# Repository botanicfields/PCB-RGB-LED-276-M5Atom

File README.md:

# PCB-RGB-LED-276-M5Atom
Circle clock using 276pcs of WS2812C-2020 and an M5Atom

## 頒布

[M5Atom 用 RGB LED 276 基板](https://www.switch-science.com/catalog/7039/)

[M5Atom 用 RGB LED 276 基板（丸形）](https://botanicfields.booth.pm/items/2940057)

## 説明書

https://github.com/botanicfields/PCB-RGB-LED-276-M5Atom/blob/main/bf-025_doc.pdf

## RTC 基板の増設

　GROVE コネクタ経由でリアルタイムクロック (RTC) 基板を増設できます。スペーサを用いて 2 階建てにできます。

[M5 用 リアルタイムクロック (RTC) 基板](https://www.switch-science.com/catalog/7170/)

## 置時計のデモ
　置時計のデモを作成しました。RTC に対応しました。RTC がなくても動作します。以下の機能があります。

- 時・分・秒・曜日・年・月・日の表示（スクロール）
- 時・分・秒のアナログ風表示（彗星の尾）
- 文字盤背景色の変化
- デモ: 時刻表示中のデモ (DemoClock)
- デモ: カウントダウンタイマー (DemoTimeShock)
- デモ: ランプテスト表示 (DemoCyron)
- デモ: 色相環表示 (DemoHueRing)
- デモ: パーリンノイズ (DemoNoise)

　時刻表示中のデモには以下があります。

- 文字色の切替（シアン・赤・緑・青）
- フォント表示（記号・数字、英大文字、英小文字）
- テキスト表示（英大文字、英小文字混在）
- エイリアン

　動作中 M5Atom のボタンで以下を操作します。切替の状況はシリアルモニタで確認できます。

|長押し時間|表示|効果|
|:-:|:-:|:-:|
| -  |Pale|カラーパレットを切替|
|>1 秒|Next|デモを切替、【クロックデモ】デモ内容を切替（文字色、フォント）|
|>2 秒|Exit|デモを切替|
|>3 秒|Temp|色温度を切替|
|>4 秒|Corr|色補正を切替|
|>5 秒|Scal|【パーリンノイズデモ】スケール (x, y) を切替|
|>6 秒|Peri|【パーリンノイズデモ】周期 (z) を切替|
|>7 秒|Null|ボタン操作を取消|

　カウントダウンタイマー動作中、M5Atom のボタンで以下を操作します。

|長押し時間|表示|状態|効果|
|:-:|:-:|:-:|:-:|
| - | - |カウントダウン停止中|カウントダウン開始|
| - | - |カウントダウン中|クイズモードに移行、賞金額を表示|
|>1 秒|Stop| - |カウントダウンを中止、初期値に戻す|
|>2 秒|Time| - |カウントダウンを中止、初期値を変更|
|>3 秒|Pale| - |カラーパレットを変更|
|>4 秒|Exit| - |終了、デモを切替|
|>5 秒|Null| - |ボタン操作を取消|

## 解説 Explanation
"Circle LED Clock by M5Atom and FastLED" in Japanese

[M5Atom と FastLED で 円形 LED 時計を作る](https://qiita.com/BotanicFields/items/a1e182f418d5a07120ac)

## YouTube: Clock Demonstration 

[Clock Demo on BF-025: RGB-LED 276 for M5Atom](https://youtu.be/55dffut1Fk0)

## 3D images by KiCad:

## YouTube: Examples

[ColorPalette an example from FastLED on BF-025: RGB-LED 276 for M5Atom](https://youtu.be/OUliTGfqcDM)

[DemoReel100 an example from FastLED on BF-025 RGB-LED 276 for M5Atom](https://youtu.be/VHuoHDQSU5E)

[Pacifica an example from FastLED on BF-025 RGB-LED 276 for M5Atom](https://youtu.be/MY5FGuDM8ZY)

[Pride2015 an example from FastLED on BF-025: RGB-LED 276 for M5Atom](https://youtu.be/uj7ePEQMkhk)

[TwinkleFox an exmaple from FastLED on BF025: RGB-LED 276 for M5Atom](https://youtu.be/3NwbCFiiEbc)

## Discussions

[JLCPCB official user group facebook](https://www.facebook.com/groups/JLCPCB/permalink/837468943770299/)

## Practical status of gerber, BOM, pick & place

### V02L01

- JLCPCB: OK

### V03L01

- ALLPCB: OK
- Seeed FusionPCB: OK

### V03L02

- ALLPCB: OK
- JLCPCB: OK

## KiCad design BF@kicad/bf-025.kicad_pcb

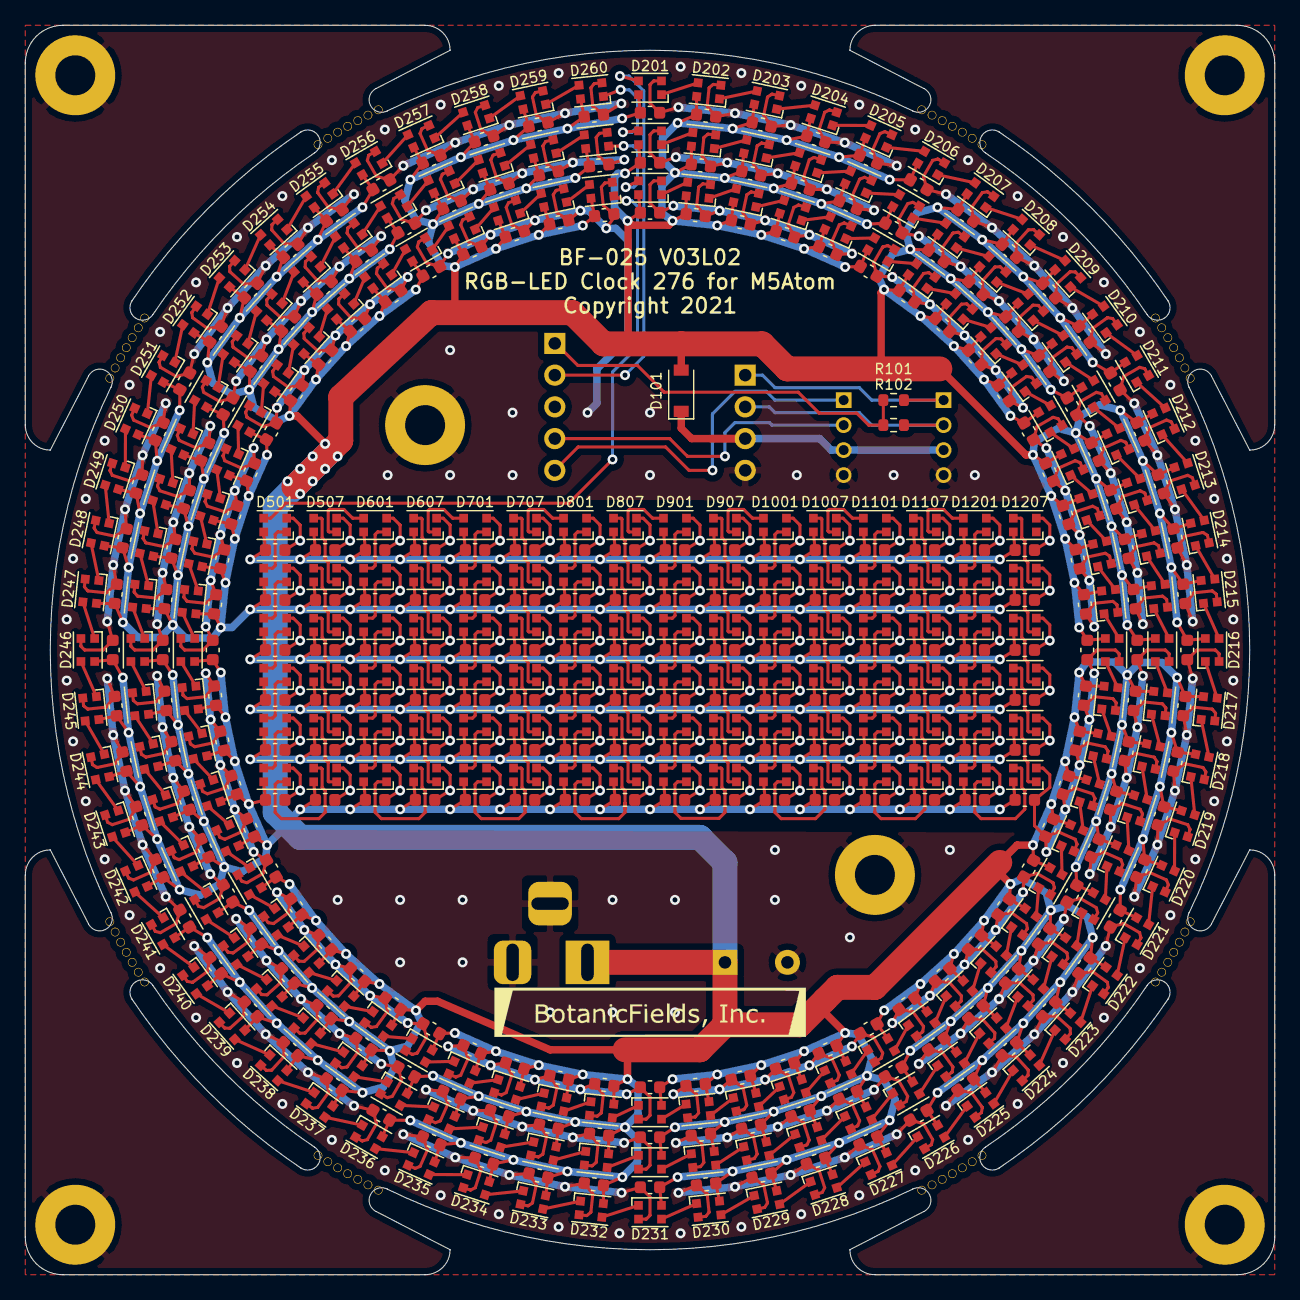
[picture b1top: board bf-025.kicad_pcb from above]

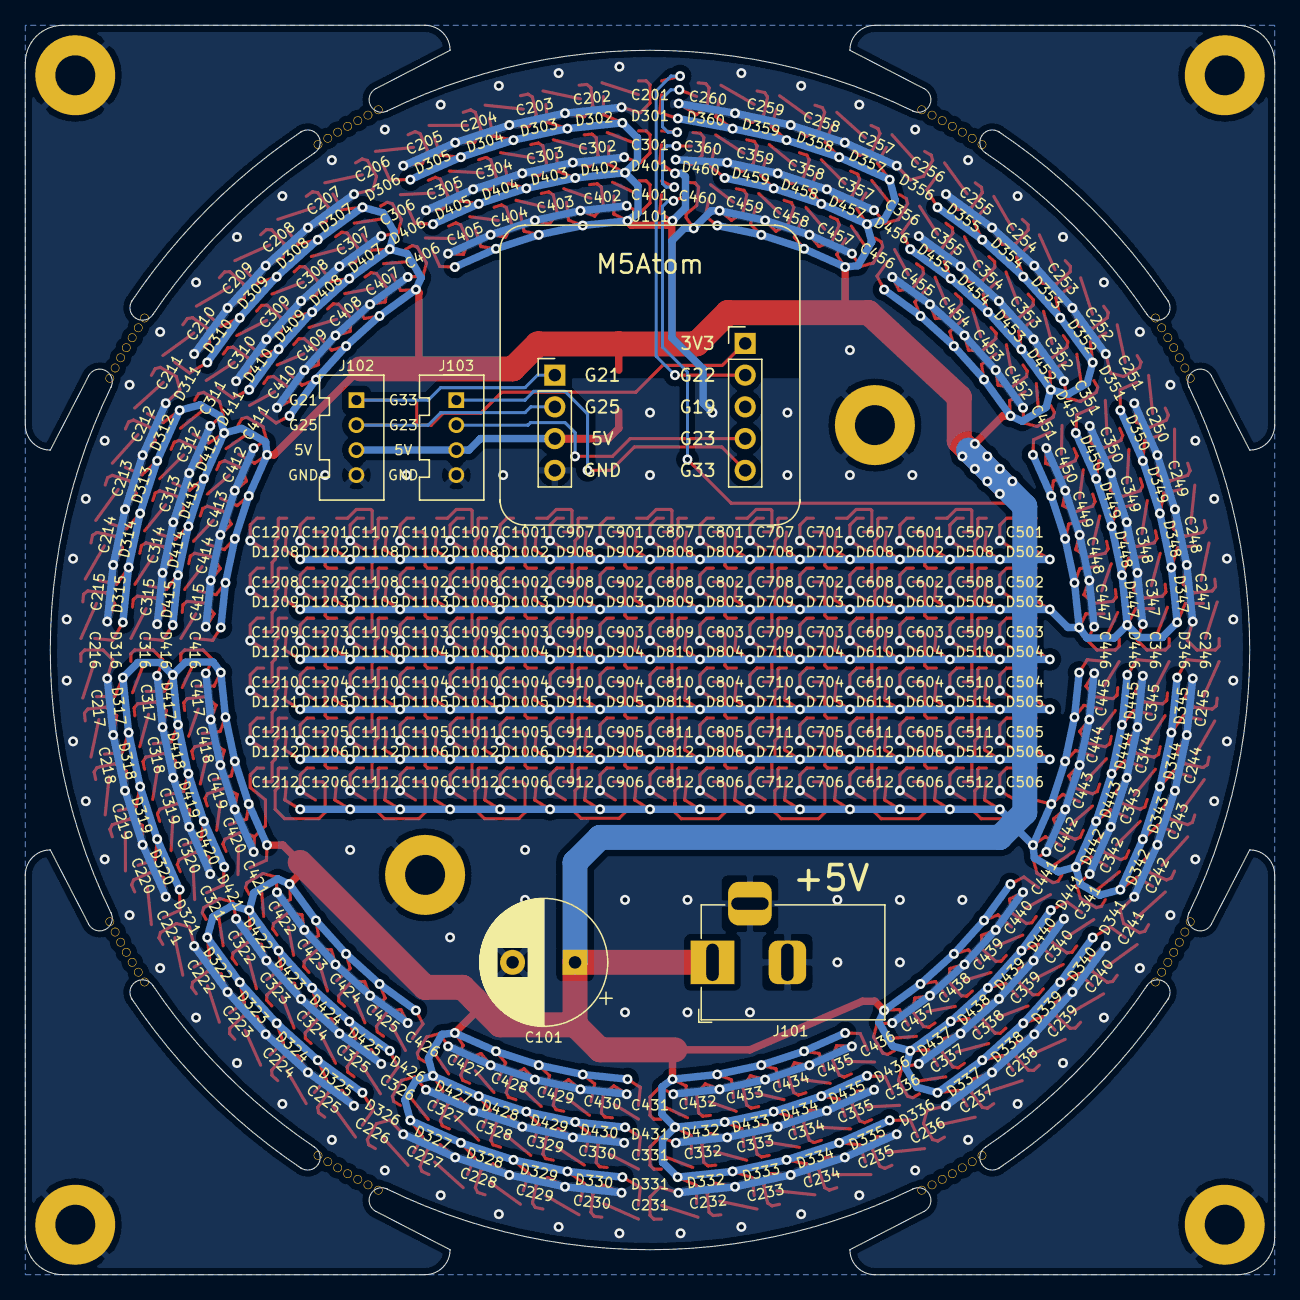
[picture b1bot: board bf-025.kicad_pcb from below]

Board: 2 copper layers, 100.0 x 100.0 mm, 560 parts (5 on the bottom side), 284 nets.

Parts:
C101: 1000u; CP_Radial_D10.0mm_P5.00mm
C201, C202, C203, C204, C205, C206, C207, C208, C209, C210, C211, C212, C213, C214, C215, C216, C217, C218, C219, C220, C221, C222, C223, C224, C225, C226, C227, C228, C229, C230, C231, C232, C233, C234, C235, C236, C237, C238, C239, C240, C241, C242, C243, C244, C245, C246, C247, C248, C249, C250, C251, C252, C253, C254, C255, C256, C257, C258, C259, C260, C301, C302, C303, C304, C305, C306, C307, C308, C309, C310, C311, C312, C313, C314, C315, C316, C317, C318, C319, C320, C321, C322, C323, C324, C325, C326, C327, C328, C329, C330, C331, C332, C333, C334, C335, C336, C337, C338, C339, C340, C341, C342, C343, C344, C345, C346, C347, C348, C349, C350, C351, C352, C353, C354, C355, C356, C357, C358, C359, C360, C401, C402, C403, C404, C405, C406, C407, C408, C409, C410, C411, C412, C413, C414, C415, C416, C417, C418, C419, C420, C421, C422, C423, C424, C425, C426, C427, C428, C429, C430, C431, C432, C433, C434, C435, C436, C437, C438, C439, C440, C441, C442, C443, C444, C445, C446, C447, C448, C449, C450, C451, C452, C453, C454, C455, C456, C457, C458, C459, C460, C501, C502, C503, C504, C505, C506, C507, C508, C509, C510, C511, C512, C601, C602, C603, C604, C605, C606, C607, C608, C609, C610, C611, C612, C701, C702, C703, C704, C705, C706, C707, C708, C709, C710, C711, C712, C801, C802, C803, C804, C805, C806, C807, C808, C809, C810, C811, C812, C901, C902, C903, C904, C905, C906, C907, C908, C909, C910, C911, C912, C1001, C1002, C1003, C1004, C1005, C1006, C1007, C1008, C1009, C1010, C1011, C1012, C1101, C1102, C1103, C1104, C1105, C1106, C1107, C1108, C1109, C1110, C1111, C1112, C1201, C1202, C1203, C1204, C1205, C1206, C1207, C1208, C1209, C1210, C1211, C1212: 100n; C_0603_1608Metric
D101: B5819W; D_SOD-123
D201, D202, D203, D204, D205, D206, D207, D208, D209, D210, D211, D212, D213, D214, D215, D216, D217, D218, D219, D220, D221, D222, D223, D224, D225, D226, D227, D228, D229, D230, D231, D232, D233, D234, D235, D236, D237, D238, D239, D240, D241, D242, D243, D244, D245, D246, D247, D248, D249, D250, D251, D252, D253, D254, D255, D256, D257, D258, D259, D260, D301, D302, D303, D304, D305, D306, D307, D308, D309, D310, D311, D312, D313, D314, D315, D316, D317, D318, D319, D320, D321, D322, D323, D324, D325, D326, D327, D328, D329, D330, D331, D332, D333, D334, D335, D336, D337, D338, D339, D340, D341, D342, D343, D344, D345, D346, D347, D348, D349, D350, D351, D352, D353, D354, D355, D356, D357, D358, D359, D360, D401, D402, D403, D404, D405, D406, D407, D408, D409, D410, D411, D412, D413, D414, D415, D416, D417, D418, D419, D420, D421, D422, D423, D424, D425, D426, D427, D428, D429, D430, D431, D432, D433, D434, D435, D436, D437, D438, D439, D440, D441, D442, D443, D444, D445, D446, D447, D448, D449, D450, D451, D452, D453, D454, D455, D456, D457, D458, D459, D460, D501, D502, D503, D504, D505, D506, D507, D508, D509, D510, D511, D512, D601, D602, D603, D604, D605, D606, D607, D608, D609, D610, D611, D612, D701, D702, D703, D704, D705, D706, D707, D708, D709, D710, D711, D712, D801, D802, D803, D804, D805, D806, D807, D808, D809, D810, D811, D812, D901, D902, D903, D904, D905, D906, D907, D908, D909, D910, D911, D912, D1001, D1002, D1003, D1004, D1005, D1006, D1007, D1008, D1009, D1010, D1011, D1012, D1101, D1102, D1103, D1104, D1105, D1106, D1107, D1108, D1109, D1110, D1111, D1112, D1201, D1202, D1203, D1204, D1205, D1206, D1207, D1208, D1209, D1210, D1211, D1212: WS2812C-2020; BF@WS2812C-2020
J101: Barrel_Jack_Switch; BF@BarrelJack_Horizontal
J102: I2C; HW4-2.0
J103: UART; HW4-2.0
R101, R102: 10k; R_0603_1608Metric
U101: M5Atom; BF@M5Atom

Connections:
+5V: C101.1, C201.1, C202.1, C203.1, C204.1, C205.1, C206.1, C207.1, C208.1, C209.1, C210.1, C211.1, C212.1, C213.1, C214.1, C215.1, C216.1, C217.1, C218.1, C219.1, C220.1, C221.1, C222.1, C223.1, C224.1, C225.1, C226.1, C227.1, C228.1, C229.1, C230.1, C231.1, C232.1, C233.1, C234.1, C235.1, C236.1, C237.1, C238.1, C239.1, C240.1, C241.1, C242.1, C243.1, C244.1, C245.1, C246.1, C247.1, C248.1, C249.1, C250.1, C251.1, C252.1, C253.1, C254.1, C255.1, C256.1, C257.1, C258.1, C259.1, C260.1, C301.1, C302.1, C303.1, C304.1, C305.1, C306.1, C307.1, C308.1, C309.1, C310.1, C311.1, C312.1, C313.1, C314.1, C315.1, C316.1, C317.1, C318.1, C319.1, C320.1, C321.1, C322.1, C323.1, C324.1, C325.1, C326.1, C327.1, C328.1, C329.1, C330.1, C331.1, C332.1, C333.1, C334.1, C335.1, C336.1, C337.1, C338.1, C339.1, C340.1, C341.1, C342.1, C343.1, C344.1, C345.1, C346.1, C347.1, C348.1, C349.1, C350.1, C351.1, C352.1, C353.1, C354.1, C355.1, C356.1, C357.1, C358.1, C359.1, C360.1, C401.1, C402.1, C403.1, C404.1, C405.1, C406.1, C407.1, C408.1, C409.1, C410.1, C411.1, C412.1, C413.1, C414.1, C415.1, C416.1, C417.1, C418.1, C419.1, C420.1, C421.1, C422.1, C423.1, C424.1, C425.1, C426.1, C427.1, C428.1, C429.1, C430.1, C431.1, C432.1, C433.1, C434.1, C435.1, C436.1, C437.1, C438.1, C439.1, C440.1, C441.1, C442.1, C443.1, C444.1, C445.1, C446.1, C447.1, C448.1, C449.1, C450.1, C451.1, C452.1, C453.1, C454.1, C455.1, C456.1, C457.1, C458.1, C459.1, C460.1, C501.1, C502.1, C503.1, C504.1, C505.1, C506.1, C507.1, C508.1, C509.1, C510.1, C511.1, C512.1, C601.1, C602.1, C603.1, C604.1, C605.1, C606.1, C607.1, C608.1, C609.1, C610.1, C611.1, C612.1, C701.1, C702.1, C703.1, C704.1, C705.1, C706.1, C707.1, C708.1, C709.1, C710.1, C711.1, C712.1, C801.1, C802.1, C803.1, C804.1, C805.1, C806.1, C807.1, C808.1, C809.1, C810.1, C811.1, C812.1, C901.1, C902.1, C903.1, C904.1, C905.1, C906.1, C907.1, C908.1, C909.1, C910.1, C911.1, C912.1, C1001.1, C1002.1, C1003.1, C1004.1, C1005.1, C1006.1, C1007.1, C1008.1, C1009.1, C1010.1, C1011.1, C1012.1, C1101.1, C1102.1, C1103.1, C1104.1, C1105.1, C1106.1, C1107.1, C1108.1, C1109.1, C1110.1, C1111.1, C1112.1, C1201.1, C1202.1, C1203.1, C1204.1, C1205.1, C1206.1, C1207.1, C1208.1, C1209.1, C1210.1, C1211.1, C1212.1, D101.2, D201.4, D202.4, D203.4, D204.4, D205.4, D206.4, D207.4, D208.4, D209.4, D210.4, D211.4, D212.4, D213.4, D214.4, D215.4, D216.4, D217.4, D218.4, D219.4, D220.4, D221.4, D222.4, D223.4, D224.4, D225.4, D226.4, D227.4, D228.4, D229.4, D230.4, D231.4, D232.4, D233.4, D234.4, D235.4, D236.4, D237.4, D238.4, D239.4, D240.4, D241.4, D242.4, D243.4, D244.4, D245.4, D246.4, D247.4, D248.4, D249.4, D250.4, D251.4, D252.4, D253.4, D254.4, D255.4, D256.4, D257.4, D258.4, D259.4, D260.4, D301.4, D302.4, D303.4, D304.4, D305.4, D306.4, D307.4, D308.4, D309.4, D310.4, D311.4, D312.4, D313.4, D314.4, D315.4, D316.4, D317.4, D318.4, D319.4, D320.4, D321.4, D322.4, D323.4, D324.4, D325.4, D326.4, D327.4, D328.4, D329.4, D330.4, D331.4, D332.4, D333.4, D334.4, D335.4, D336.4, D337.4, D338.4, D339.4, D340.4, D341.4, D342.4, D343.4, D344.4, D345.4, D346.4, D347.4, D348.4, D349.4, D350.4, D351.4, D352.4, D353.4, D354.4, D355.4, D356.4, D357.4, D358.4, D359.4, D360.4, D401.4, D402.4, D403.4, D404.4, D405.4, D406.4, D407.4, D408.4, D409.4, D410.4, D411.4, D412.4, D413.4, D414.4, D415.4, D416.4, D417.4, D418.4, D419.4, D420.4, D421.4, D422.4, D423.4, D424.4, D425.4, D426.4, D427.4, D428.4, D429.4, D430.4, D431.4, D432.4, D433.4, D434.4, D435.4, D436.4, D437.4, D438.4, D439.4, D440.4, D441.4, D442.4, D443.4, D444.4, D445.4, D446.4, D447.4, D448.4, D449.4, D450.4, D451.4, D452.4, D453.4, D454.4, D455.4, D456.4, D457.4, D458.4, D459.4, D460.4, D501.4, D502.4, D503.4, D504.4, D505.4, D506.4, D507.4, D508.4, D509.4, D510.4, D511.4, D512.4, D601.4, D602.4, D603.4, D604.4, D605.4, D606.4, D607.4, D608.4, D609.4, D610.4, D611.4, D612.4, D701.4, D702.4, D703.4, D704.4, D705.4, D706.4, D707.4, D708.4, D709.4, D710.4, D711.4, D712.4, D801.4, D802.4, D803.4, D804.4, D805.4, D806.4, D807.4, D808.4, D809.4, D810.4, D811.4, D812.4, D901.4, D902.4, D903.4, D904.4, D905.4, D906.4, D907.4, D908.4, D909.4, D910.4, D911.4, D912.4, D1001.4, D1002.4, D1003.4, D1004.4, D1005.4, D1006.4, D1007.4, D1008.4, D1009.4, D1010.4, D1011.4, D1012.4, D1101.4, D1102.4, D1103.4, D1104.4, D1105.4, D1106.4, D1107.4, D1108.4, D1109.4, D1110.4, D1111.4, D1112.4, D1201.4, D1202.4, D1203.4, D1204.4, D1205.4, D1206.4, D1207.4, D1208.4, D1209.4, D1210.4, D1211.4, D1212.4, J101.1
/G21: J102.1, R101.2, U101.1
/G23_G34: J103.2, U101.6
/G25: J102.2, R102.2, U101.2
/G33: J103.1, U101.5
/M5_3V3: R101.1, R102.1, U101.9
/M5_5V: D101.1, J102.3, J103.3, U101.3
/WS2812C_12_1/DI: D460.1, D501.3
/WS2812C_12_2/DI: D507.1, D601.3
/WS2812C_12_3/DI: D607.1, D701.3
/WS2812C_12_4/DI: D707.1, D801.3
/WS2812C_12_5/DI: D807.1, D901.3
/WS2812C_12_6/DI: D907.1, D1001.3
/WS2812C_12_7/DI: D1007.1, D1101.3
/WS2812C_12_8/DI: D1107.1, D1201.3
/WS2812C_60_1/DIN: D201.3, U101.8
/WS2812C_60_2/DIN: D260.1, D301.3
/WS2812C_60_3/DIN: D360.1, D401.3
GND: C101.2, C201.2, C202.2, C203.2, C204.2, C205.2, C206.2, C207.2, C208.2, C209.2, C210.2, C211.2, C212.2, C213.2, C214.2, C215.2, C216.2, C217.2, C218.2, C219.2, C220.2, C221.2, C222.2, C223.2, C224.2, C225.2, C226.2, C227.2, C228.2, C229.2, C230.2, C231.2, C232.2, C233.2, C234.2, C235.2, C236.2, C237.2, C238.2, C239.2, C240.2, C241.2, C242.2, C243.2, C244.2, C245.2, C246.2, C247.2, C248.2, C249.2, C250.2, C251.2, C252.2, C253.2, C254.2, C255.2, C256.2, C257.2, C258.2, C259.2, C260.2, C301.2, C302.2, C303.2, C304.2, C305.2, C306.2, C307.2, C308.2, C309.2, C310.2, C311.2, C312.2, C313.2, C314.2, C315.2, C316.2, C317.2, C318.2, C319.2, C320.2, C321.2, C322.2, C323.2, C324.2, C325.2, C326.2, C327.2, C328.2, C329.2, C330.2, C331.2, C332.2, C333.2, C334.2, C335.2, C336.2, C337.2, C338.2, C339.2, C340.2, C341.2, C342.2, C343.2, C344.2, C345.2, C346.2, C347.2, C348.2, C349.2, C350.2, C351.2, C352.2, C353.2, C354.2, C355.2, C356.2, C357.2, C358.2, C359.2, C360.2, C401.2, C402.2, C403.2, C404.2, C405.2, C406.2, C407.2, C408.2, C409.2, C410.2, C411.2, C412.2, C413.2, C414.2, C415.2, C416.2, C417.2, C418.2, C419.2, C420.2, C421.2, C422.2, C423.2, C424.2, C425.2, C426.2, C427.2, C428.2, C429.2, C430.2, C431.2, C432.2, C433.2, C434.2, C435.2, C436.2, C437.2, C438.2, C439.2, C440.2, C441.2, C442.2, C443.2, C444.2, C445.2, C446.2, C447.2, C448.2, C449.2, C450.2, C451.2, C452.2, C453.2, C454.2, C455.2, C456.2, C457.2, C458.2, C459.2, C460.2, C501.2, C502.2, C503.2, C504.2, C505.2, C506.2, C507.2, C508.2, C509.2, C510.2, C511.2, C512.2, C601.2, C602.2, C603.2, C604.2, C605.2, C606.2, C607.2, C608.2, C609.2, C610.2, C611.2, C612.2, C701.2, C702.2, C703.2, C704.2, C705.2, C706.2, C707.2, C708.2, C709.2, C710.2, C711.2, C712.2, C801.2, C802.2, C803.2, C804.2, C805.2, C806.2, C807.2, C808.2, C809.2, C810.2, C811.2, C812.2, C901.2, C902.2, C903.2, C904.2, C905.2, C906.2, C907.2, C908.2, C909.2, C910.2, C911.2, C912.2, C1001.2, C1002.2, C1003.2, C1004.2, C1005.2, C1006.2, C1007.2, C1008.2, C1009.2, C1010.2, C1011.2, C1012.2, C1101.2, C1102.2, C1103.2, C1104.2, C1105.2, C1106.2, C1107.2, C1108.2, C1109.2, C1110.2, C1111.2, C1112.2, C1201.2, C1202.2, C1203.2, C1204.2, C1205.2, C1206.2, C1207.2, C1208.2, C1209.2, C1210.2, C1211.2, C1212.2, D201.2, D202.2, D203.2, D204.2, D205.2, D206.2, D207.2, D208.2, D209.2, D210.2, D211.2, D212.2, D213.2, D214.2, D215.2, D216.2, D217.2, D218.2, D219.2, D220.2, D221.2, D222.2, D223.2, D224.2, D225.2, D226.2, D227.2, D228.2, D229.2, D230.2, D231.2, D232.2, D233.2, D234.2, D235.2, D236.2, D237.2, D238.2, D239.2, D240.2, D241.2, D242.2, D243.2, D244.2, D245.2, D246.2, D247.2, D248.2, D249.2, D250.2, D251.2, D252.2, D253.2, D254.2, D255.2, D256.2, D257.2, D258.2, D259.2, D260.2, D301.2, D302.2, D303.2, D304.2, D305.2, D306.2, D307.2, D308.2, D309.2, D310.2, D311.2, D312.2, D313.2, D314.2, D315.2, D316.2, D317.2, D318.2, D319.2, D320.2, D321.2, D322.2, D323.2, D324.2, D325.2, D326.2, D327.2, D328.2, D329.2, D330.2, D331.2, D332.2, D333.2, D334.2, D335.2, D336.2, D337.2, D338.2, D339.2, D340.2, D341.2, D342.2, D343.2, D344.2, D345.2, D346.2, D347.2, D348.2, D349.2, D350.2, D351.2, D352.2, D353.2, D354.2, D355.2, D356.2, D357.2, D358.2, D359.2, D360.2, D401.2, D402.2, D403.2, D404.2, D405.2, D406.2, D407.2, D408.2, D409.2, D410.2, D411.2, D412.2, D413.2, D414.2, D415.2, D416.2, D417.2, D418.2, D419.2, D420.2, D421.2, D422.2, D423.2, D424.2, D425.2, D426.2, D427.2, D428.2, D429.2, D430.2, D431.2, D432.2, D433.2, D434.2, D435.2, D436.2, D437.2, D438.2, D439.2, D440.2, D441.2, D442.2, D443.2, D444.2, D445.2, D446.2, D447.2, D448.2, D449.2, D450.2, D451.2, D452.2, D453.2, D454.2, D455.2, D456.2, D457.2, D458.2, D459.2, D460.2, D501.2, D502.2, D503.2, D504.2, D505.2, D506.2, D507.2, D508.2, D509.2, D510.2, D511.2, D512.2, D601.2, D602.2, D603.2, D604.2, D605.2, D606.2, D607.2, D608.2, D609.2, D610.2, D611.2, D612.2, D701.2, D702.2, D703.2, D704.2, D705.2, D706.2, D707.2, D708.2, D709.2, D710.2, D711.2, D712.2, D801.2, D802.2, D803.2, D804.2, D805.2, D806.2, D807.2, D808.2, D809.2, D810.2, D811.2, D812.2, D901.2, D902.2, D903.2, D904.2, D905.2, D906.2, D907.2, D908.2, D909.2, D910.2, D911.2, D912.2, D1001.2, D1002.2, D1003.2, D1004.2, D1005.2, D1006.2, D1007.2, D1008.2, D1009.2, D1010.2, D1011.2, D1012.2, D1101.2, D1102.2, D1103.2, D1104.2, D1105.2, D1106.2, D1107.2, D1108.2, D1109.2, D1110.2, D1111.2, D1112.2, D1201.2, D1202.2, D1203.2, D1204.2, D1205.2, D1206.2, D1207.2, D1208.2, D1209.2, D1210.2, D1211.2, D1212.2, J101.2, J101.3, J102.4, J103.4, U101.4
unnamed: D201.1, D202.3
unnamed: D202.1, D203.3
unnamed: D203.1, D204.3
unnamed: D204.1, D205.3
unnamed: D205.1, D206.3
unnamed: D206.1, D207.3
unnamed: D207.1, D208.3
unnamed: D208.1, D209.3
unnamed: D209.1, D210.3
unnamed: D210.1, D211.3
unnamed: D211.1, D212.3
unnamed: D212.1, D213.3
unnamed: D213.1, D214.3
unnamed: D214.1, D215.3
unnamed: D215.1, D216.3
unnamed: D216.1, D217.3
unnamed: D217.1, D218.3
unnamed: D218.1, D219.3
unnamed: D219.1, D220.3
unnamed: D220.1, D221.3
unnamed: D221.1, D222.3
unnamed: D222.1, D223.3
unnamed: D223.1, D224.3
unnamed: D224.1, D225.3
unnamed: D225.1, D226.3
unnamed: D226.1, D227.3
unnamed: D227.1, D228.3
unnamed: D228.1, D229.3
unnamed: D229.1, D230.3
unnamed: D230.1, D231.3
unnamed: D231.1, D232.3
unnamed: D232.1, D233.3
unnamed: D233.1, D234.3
unnamed: D234.1, D235.3
unnamed: D235.1, D236.3
unnamed: D236.1, D237.3
unnamed: D237.1, D238.3
unnamed: D238.1, D239.3
unnamed: D239.1, D240.3
unnamed: D240.1, D241.3
unnamed: D241.1, D242.3
unnamed: D242.1, D243.3
unnamed: D243.1, D244.3
unnamed: D244.1, D245.3
unnamed: D245.1, D246.3
unnamed: D246.1, D247.3
unnamed: D247.1, D248.3
unnamed: D248.1, D249.3
unnamed: D249.1, D250.3
unnamed: D250.1, D251.3
unnamed: D251.1, D252.3
unnamed: D252.1, D253.3
unnamed: D253.1, D254.3
unnamed: D254.1, D255.3
unnamed: D255.1, D256.3
unnamed: D256.1, D257.3
unnamed: D257.1, D258.3
unnamed: D258.1, D259.3
unnamed: D259.1, D260.3
unnamed: D301.1, D302.3
unnamed: D302.1, D303.3
unnamed: D303.1, D304.3
unnamed: D304.1, D305.3
unnamed: D305.1, D306.3
unnamed: D306.1, D307.3
unnamed: D307.1, D308.3
unnamed: D308.1, D309.3
unnamed: D309.1, D310.3
unnamed: D310.1, D311.3
unnamed: D311.1, D312.3
unnamed: D312.1, D313.3
unnamed: D313.1, D314.3
unnamed: D314.1, D315.3
unnamed: D315.1, D316.3
unnamed: D316.1, D317.3
unnamed: D317.1, D318.3
unnamed: D318.1, D319.3
unnamed: D319.1, D320.3
unnamed: D320.1, D321.3
unnamed: D321.1, D322.3
unnamed: D322.1, D323.3
unnamed: D323.1, D324.3
unnamed: D324.1, D325.3
unnamed: D325.1, D326.3
unnamed: D326.1, D327.3
unnamed: D327.1, D328.3
unnamed: D328.1, D329.3
unnamed: D329.1, D330.3
unnamed: D330.1, D331.3
unnamed: D331.1, D332.3
unnamed: D332.1, D333.3
unnamed: D333.1, D334.3
unnamed: D334.1, D335.3
unnamed: D335.1, D336.3
unnamed: D336.1, D337.3
unnamed: D337.1, D338.3
unnamed: D338.1, D339.3
unnamed: D339.1, D340.3
unnamed: D340.1, D341.3
unnamed: D341.1, D342.3
unnamed: D342.1, D343.3
unnamed: D343.1, D344.3
unnamed: D344.1, D345.3
unnamed: D345.1, D346.3
unnamed: D346.1, D347.3
unnamed: D347.1, D348.3
unnamed: D348.1, D349.3
unnamed: D349.1, D350.3
unnamed: D350.1, D351.3
unnamed: D351.1, D352.3
unnamed: D352.1, D353.3
unnamed: D353.1, D354.3
unnamed: D354.1, D355.3
unnamed: D355.1, D356.3
unnamed: D356.1, D357.3
unnamed: D357.1, D358.3
unnamed: D358.1, D359.3
unnamed: D359.1, D360.3
unnamed: D401.1, D402.3
unnamed: D402.1, D403.3
unnamed: D403.1, D404.3
unnamed: D404.1, D405.3
unnamed: D405.1, D406.3
unnamed: D406.1, D407.3
unnamed: D407.1, D408.3
unnamed: D408.1, D409.3
unnamed: D409.1, D410.3
unnamed: D410.1, D411.3
unnamed: D411.1, D412.3
unnamed: D412.1, D413.3
unnamed: D413.1, D414.3
unnamed: D414.1, D415.3
unnamed: D415.1, D416.3
unnamed: D416.1, D417.3
unnamed: D417.1, D418.3
unnamed: D418.1, D419.3
unnamed: D419.1, D420.3
unnamed: D420.1, D421.3
unnamed: D421.1, D422.3
unnamed: D422.1, D423.3
unnamed: D423.1, D424.3
unnamed: D424.1, D425.3
unnamed: D425.1, D426.3
unnamed: D426.1, D427.3
unnamed: D427.1, D428.3
unnamed: D428.1, D429.3
unnamed: D429.1, D430.3
unnamed: D430.1, D431.3
unnamed: D431.1, D432.3
unnamed: D432.1, D433.3
unnamed: D433.1, D434.3
unnamed: D434.1, D435.3
unnamed: D435.1, D436.3
unnamed: D436.1, D437.3
unnamed: D437.1, D438.3
unnamed: D438.1, D439.3
unnamed: D439.1, D440.3
unnamed: D440.1, D441.3
unnamed: D441.1, D442.3
unnamed: D442.1, D443.3
unnamed: D443.1, D444.3
unnamed: D444.1, D445.3
unnamed: D445.1, D446.3
unnamed: D446.1, D447.3
unnamed: D447.1, D448.3
unnamed: D448.1, D449.3
unnamed: D449.1, D450.3
unnamed: D450.1, D451.3
unnamed: D451.1, D452.3
unnamed: D452.1, D453.3
unnamed: D453.1, D454.3
unnamed: D454.1, D455.3
unnamed: D455.1, D456.3
unnamed: D456.1, D457.3
unnamed: D457.1, D458.3
unnamed: D458.1, D459.3
unnamed: D459.1, D460.3
unnamed: D501.1, D502.3
unnamed: D502.1, D503.3
unnamed: D503.1, D504.3
unnamed: D504.1, D505.3
unnamed: D505.1, D506.3
unnamed: D506.1, D512.3
unnamed: D507.3, D508.1
unnamed: D508.3, D509.1
unnamed: D509.3, D510.1
unnamed: D510.3, D511.1
unnamed: D511.3, D512.1
unnamed: D601.1, D602.3
unnamed: D602.1, D603.3
unnamed: D603.1, D604.3
unnamed: D604.1, D605.3
unnamed: D605.1, D606.3
unnamed: D606.1, D612.3
unnamed: D607.3, D608.1
unnamed: D608.3, D609.1
unnamed: D609.3, D610.1
unnamed: D610.3, D611.1
unnamed: D611.3, D612.1
unnamed: D701.1, D702.3
unnamed: D702.1, D703.3
unnamed: D703.1, D704.3
unnamed: D704.1, D705.3
unnamed: D705.1, D706.3
unnamed: D706.1, D712.3
unnamed: D707.3, D708.1
unnamed: D708.3, D709.1
unnamed: D709.3, D710.1
unnamed: D710.3, D711.1
unnamed: D711.3, D712.1
unnamed: D801.1, D802.3
unnamed: D802.1, D803.3
unnamed: D803.1, D804.3
unnamed: D804.1, D805.3
unnamed: D805.1, D806.3
unnamed: D806.1, D812.3
unnamed: D807.3, D808.1
unnamed: D808.3, D809.1
unnamed: D809.3, D810.1
unnamed: D810.3, D811.1
unnamed: D811.3, D812.1
unnamed: D901.1, D902.3
unnamed: D902.1, D903.3
unnamed: D903.1, D904.3
unnamed: D904.1, D905.3
unnamed: D905.1, D906.3
unnamed: D906.1, D912.3
unnamed: D907.3, D908.1
unnamed: D908.3, D909.1
unnamed: D909.3, D910.1
unnamed: D910.3, D911.1
unnamed: D911.3, D912.1
unnamed: D1001.1, D1002.3
unnamed: D1002.1, D1003.3
unnamed: D1003.1, D1004.3
unnamed: D1004.1, D1005.3
unnamed: D1005.1, D1006.3
unnamed: D1006.1, D1012.3
unnamed: D1007.3, D1008.1
unnamed: D1008.3, D1009.1
unnamed: D1009.3, D1010.1
unnamed: D1010.3, D1011.1
unnamed: D1011.3, D1012.1
unnamed: D1101.1, D1102.3
unnamed: D1102.1, D1103.3
unnamed: D1103.1, D1104.3
unnamed: D1104.1, D1105.3
unnamed: D1105.1, D1106.3
unnamed: D1106.1, D1112.3
unnamed: D1107.3, D1108.1
unnamed: D1108.3, D1109.1
unnamed: D1109.3, D1110.1
unnamed: D1110.3, D1111.1
unnamed: D1111.3, D1112.1
unnamed: D1201.1, D1202.3
unnamed: D1202.1, D1203.3
unnamed: D1203.1, D1204.3
unnamed: D1204.1, D1205.3
unnamed: D1205.1, D1206.3
unnamed: D1206.1, D1212.3
unnamed: D1207.3, D1208.1
unnamed: D1208.3, D1209.1
unnamed: D1209.3, D1210.1
unnamed: D1210.3, D1211.1
unnamed: D1211.3, D1212.1

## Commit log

2021-01-10 KiCad Data
    Symbols, FootPrints, 3D
2021-01-30 PCB data
    Add PCB data of V03L01
2021-01-30 schema
    remove GND of unnecessary
2021-01-30 PCB data
    add PCB data
2021-01-30 README
    Practical Status
2021-01-31 PCB data
    footprint, 3d-omage
2021-01-31 Update README.md
    add 3D images
2021-02-02 examples
    examples from FastLED
2021-02-08 Create bf-025_led_connection.png
    description of LED connection
2021-02-11 V03L02
    update PCB layout
2021-02-11 V03L02
    update PCB
2021-02-12 gerber V03L02
    update PCB, eamples on YouTube
2021-02-12 gerber V03L02
    change filename
2021-02-18 demo codes
    update demo codes
2021-02-21 Demo-Clock
    update code
2021-02-21 Update README.md
    YouTube and Qiita
2021-03-07 demo clock
    add "Time Shock"
2021-03-07 DemoTimeShock
    update button operation
2021-03-09 photo
    add photo V03L01
2021-03-09 photo
    photo revised
2021-03-10 JPG
    update JPG
2021-03-11 document
    update document
2021-04-26 gerber V03L02
2021-05-03 Update README.md
    market place added
2021-05-05 Update bf-025_doc.pdf
    add round shaped board
2021-05-24 BF-025 demo updated
    support RTC
    improve header files
2021-05-26 RTC support
    image of RTC daughter card
2021-08-31 Noise, TimeShock
    add stand alone examples
2021-11-07 Update BF_Pcf8563.cpp
    Fix tm_mon of ReadTime().
2021-11-07 Update BF_Pcf8563.h
    add time.h
2021-11-07 Update BF-025.ino
    inactivate CLKO, INT of RTC
2021-11-07 update library
    comment out SetCountry of Wifi
    remove INT for RTC trimmer
2021-11-13 M5 Board Manager 2.0.0
    I2C process to update RTCx by SNTP callback, etc.
2021-11-13 Update BF_RtcxNtp.cpp
    activate: sntp_get_sync_interval
2021-12-18 exmaples
    add unsigned to "int last_ms"

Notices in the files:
BF@kicad/bf-025.kicad_pcb:
Copyright 2021 BotanicFields, INc.
